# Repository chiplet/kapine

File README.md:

# KAPINE
Kircular Accelerator Prototype Innovative New Experience

# Setup

## KiCAD Library Setup
Run the following command to install the third party KiCAD libraries used in the project

`git submodule update --init --recursive`

This project uses components from [digikey-kicad-library](https://github.com/Digi-Key/digikey-kicad-library) which is configured as a git submodule of this project. Git doesn't clone submodules of a project by default when the project it is cloned so this has to be done manually.

# Hardware

## Pinout

**Application Signal Descriptions**
* m[0..15] -- Electromagnet control signals
* s[0..15] -- Photogate sensor input signals
* Debug 1 -- Debug led 1
* Debug 2 -- Debug led 2
* USART1 -- Command link UART

| Microcontroller Pin | Application Signal | Direction   | Alternate Function |
|---------------------|--------------------|-------------|--------------------|
| PB5                 | m0                 | Digital out | TBD                |
| PD2                 | m1                 | Digital out | TBD                |
| PC11                | m2                 | Digital out | TBD                |
| PA12                | m3                 | Digital out | TBD                |
| PA8                 | m4                 | Digital out | TBD                |
| PC8                 | m5                 | Digital out | TBD                |
| PC6                 | m6                 | Digital out | TBD                |
| PB14                | m7                 | Digital out | TBD                |
| PB11                | m8                 | Digital out | TBD                |
| PB2                 | m9                 | Digital out | TBD                |
| PC5                 | m10                | Digital out | TBD                |
| ~~PA3~~ PA4         | m11                | Digital out | TBD                |
| PC3                 | m12                | Digital out | TBD                |
| PC1                 | m13                | Digital out | TBD                |
| PB9                 | m14                | Digital out | TBD                |
| PB7                 | m15                | Digital out | TBD                |
| PB4                 | s0                 | Digital in  | TBD                |
| ~~PC12~~ PA3        | s1                 | Digital in  | TBD                |
| PC10                | s2                 | Digital in  | TBD                |
| PA11                | s3                 | Digital in  | TBD                |
| PC9                 | s4                 | Digital in  | TBD                |
| PC7                 | s5                 | Digital in  | TBD                |
| PB15                | s6                 | Digital in  | TBD                |
| PB13                | s7                 | Digital in  | TBD                |
| PB10                | s8                 | Digital in  | TBD                |
| PB1                 | s9                 | Digital in  | TBD                |
| ~~PC4~~ PC14        | s10                | Digital in  | TBD                |
| PA2                 | s11                | Digital in  | TBD                |
| ~~PC2~~ PA5         | s12                | Digital in  | TBD                |
| PC0                 | s13                | Digital in  | TBD                |
| PB8                 | s14                | Digital in  | TBD                |
| PB6                 | s15                | Digital in  | TBD                |
| PA0                 | Debug 1            | Digital out | TBD                |
| PA1                 | Debug 2            | Digital out | TBD                |
| PA9                 | USART1_TX          | Digital out | AF7                |
| PA10                | USART1_RX          | Digital in  | AF7                |
| PC13                | RGB LEDs           | Digital out | TBD                |

### Change Log
* 2021-08-07: STM32F3 maps GPIO to EXTI interrupts based on pin number. The following changes needed to be made to support interrupts on all sensor input pins:
  * m11 (PA3 -> PA4)
  * s2 (PC10 -> PA3)
  * s12 (PC2 -> PA5)
  * s10 (PC4 -> PC14)

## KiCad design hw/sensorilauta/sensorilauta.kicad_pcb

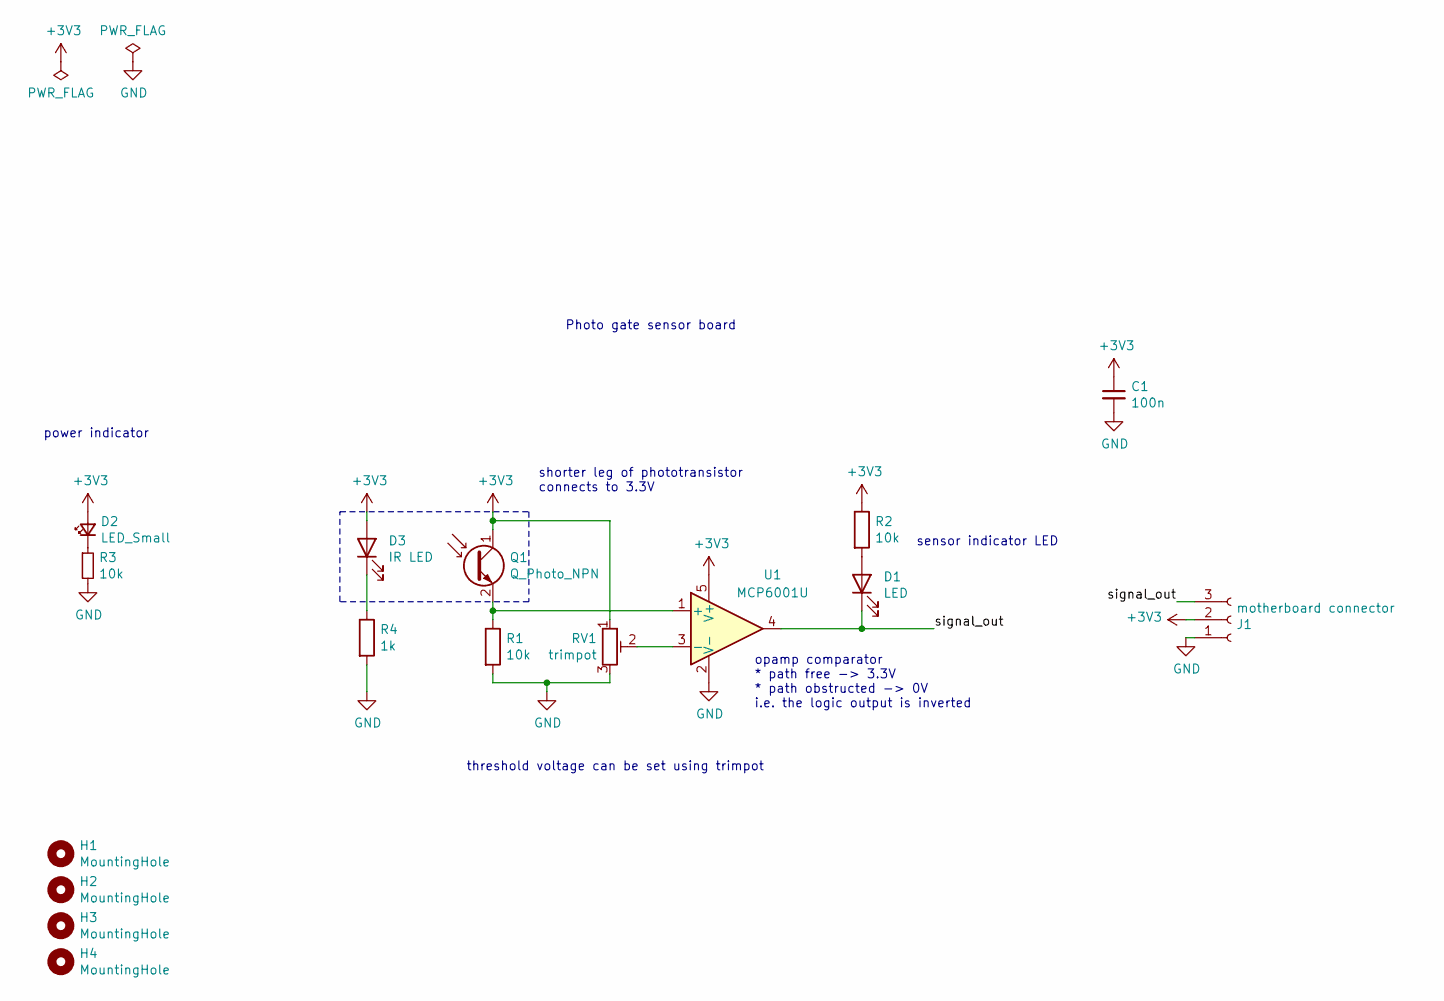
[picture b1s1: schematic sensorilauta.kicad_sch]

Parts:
C1: 100n; C_0805_2012Metric_Pad1.15x1.40mm_HandSolder
D1: LED; LED_D5.0mm
D2: LED_Small; LED_0805_2012Metric_Castellated
D3: IR LED; PinHeader_2x01_P2.54mm_Vertical
H1, H2, H3, H4: MountingHole; MountingHole_4.3mm_M4
J1: motherboard connector; PinHeader_1x03_P2.54mm_Horizontal
Q1: Q_Photo_NPN; PinHeader_2x01_P2.54mm_Vertical
R1, R2, R3: 10k; R_0805_2012Metric_Pad1.15x1.40mm_HandSolder
R4: 1k; R_0805_2012Metric_Pad1.15x1.40mm_HandSolder
RV1: trimpot; Potentiometer_Vishay_TS53YJ_Vertical
U1: MCP6001U; SOT-23-5_HandSoldering

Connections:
+3V3: C1.1, D2.2 (A), D3.2 (A), J1.2, Q1.1 (C), R2.1, RV1.1, U1.5 (V+)
/signal_out: D1.1 (K), J1.3, U1.4
GND: C1.2, J1.1, R1.2, R3.2, R4.2, RV1.3, U1.2 (V-)
unnamed: D1.2 (A), R2.2
unnamed: D2.1 (K), R3.1
unnamed: D3.1 (K), R4.1
unnamed: Q1.2 (E), R1.1, U1.1 (+)
unnamed: RV1.2, U1.3 (-)

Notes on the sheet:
power indicator
sensor indicator LED
threshold voltage can be set using trimpot
Photo gate sensor board
opamp comparator * path free -> 3.3V * path obstructed -> 0V i.e. the logic output is inverted
shorter leg of phototransistor connects to 3.3V

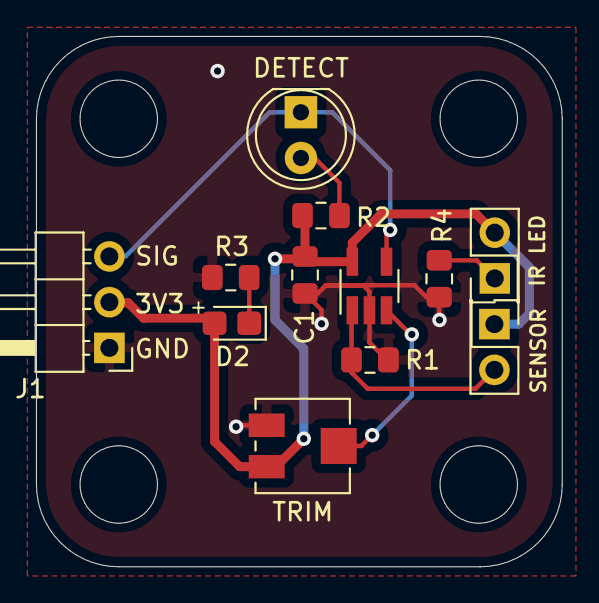
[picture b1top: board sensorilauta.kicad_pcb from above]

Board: 2 copper layers, 29.2 x 29.5 mm, 16 parts (0 on the bottom side), 8 nets.

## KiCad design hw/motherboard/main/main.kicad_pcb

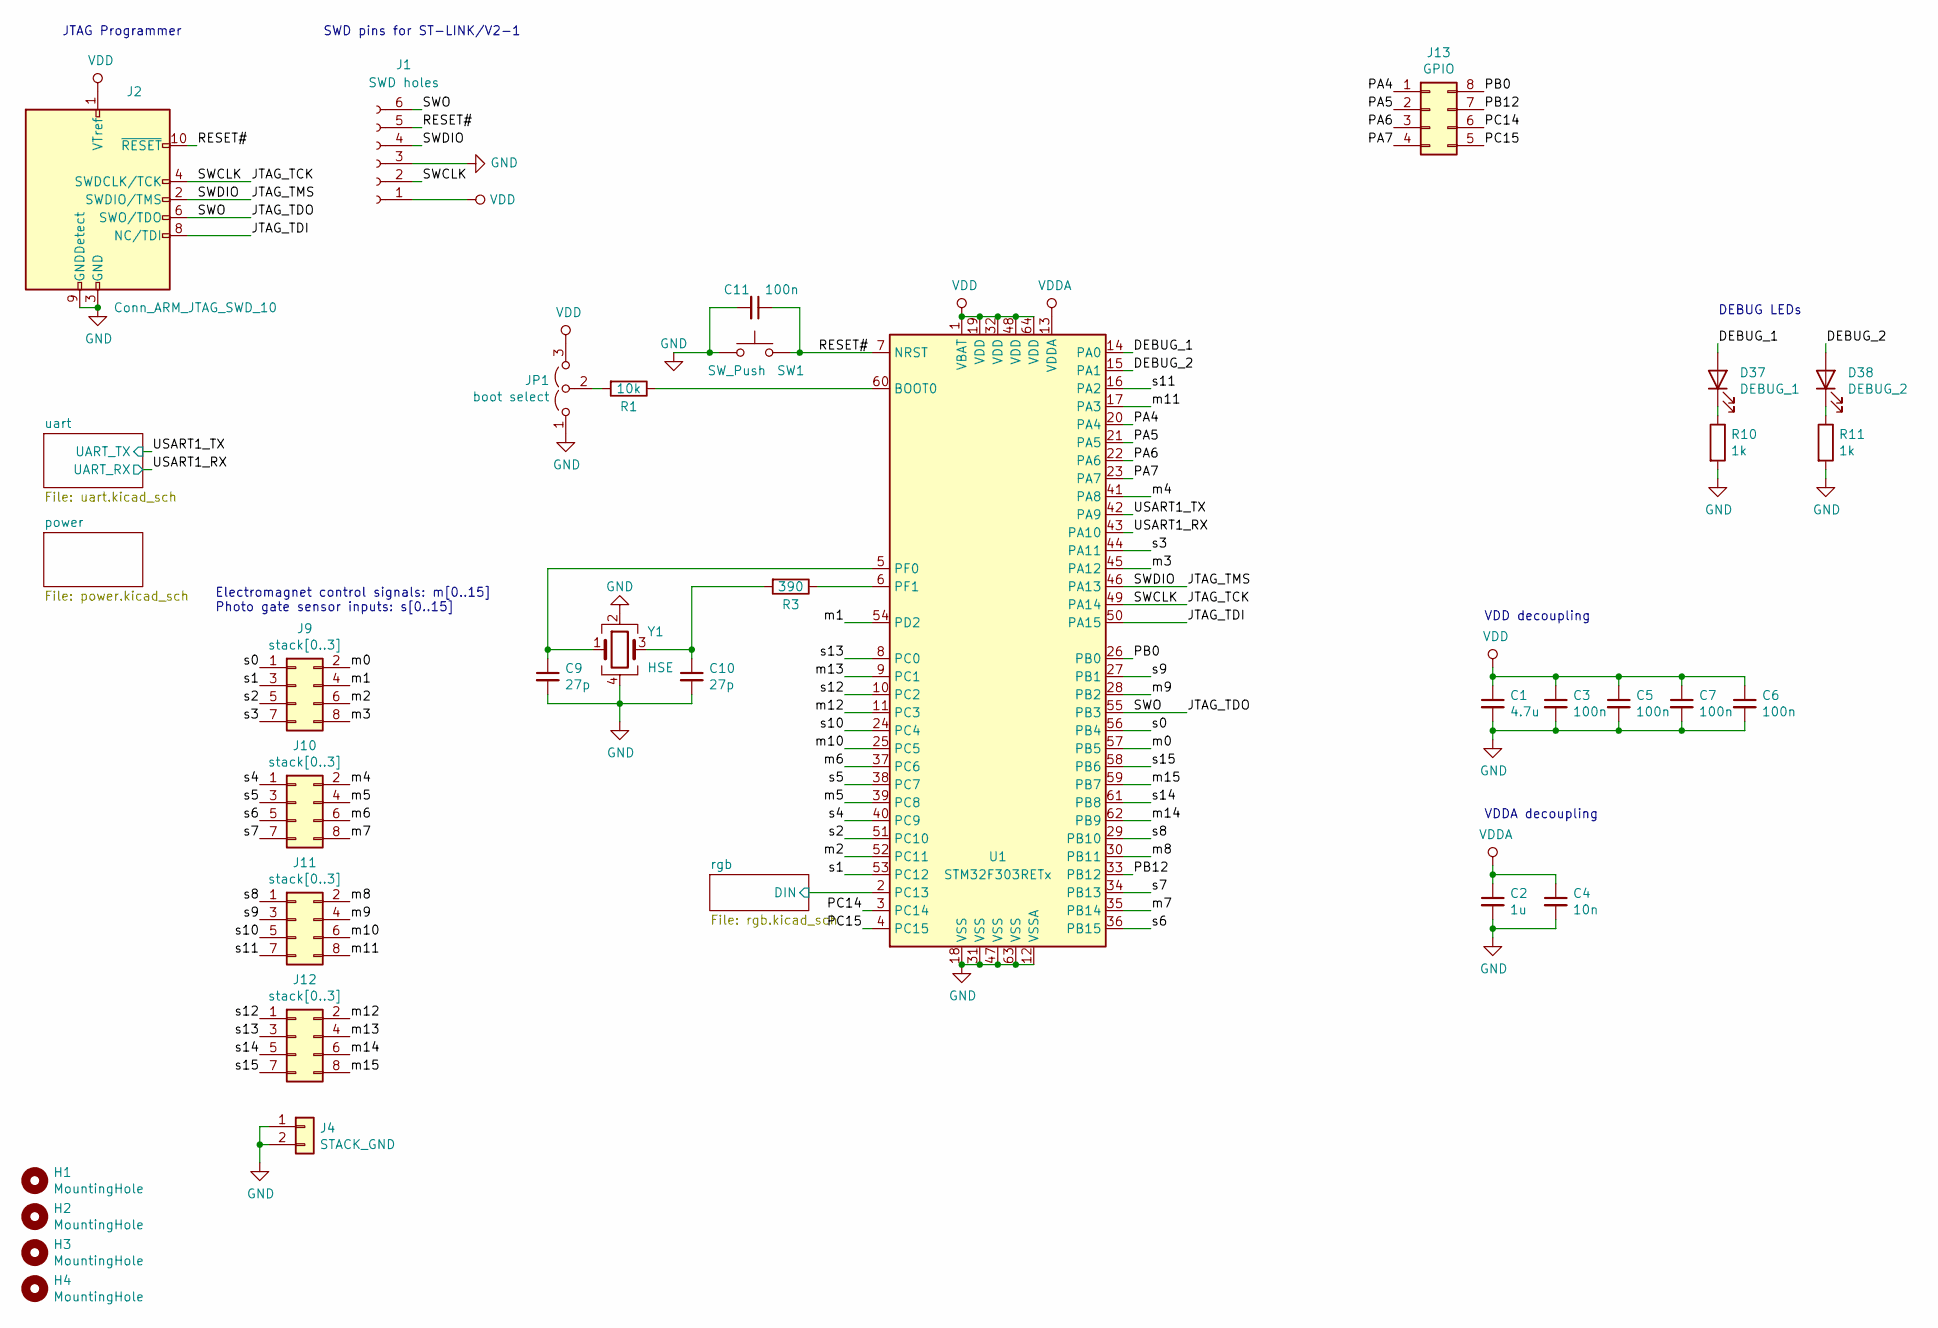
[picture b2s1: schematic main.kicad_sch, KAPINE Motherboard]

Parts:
C1: 4.7u; C_0805_2012Metric
C2: 1u; C_0603_1608Metric
C3, C5, C6, C7, C11: 100n; C_0603_1608Metric
C4: 10n; C_0603_1608Metric
C9, C10: 27p; C_0603_1608Metric
D37: DEBUG_1; LED_0805_2012Metric
D38: DEBUG_2; LED_0805_2012Metric
H1, H2, H3, H4: MountingHole; MountingHole_4.3mm_M4
J1: SWD holes; PinHeader_1x06_P2.54mm_Vertical
J2: Conn_ARM_JTAG_SWD_10; PinHeader_2x5_P1.27mm_Drill.7mm
J4: STACK_GND; PinSocket_1x02_P2.54mm_Vertical
J9, J10, J11, J12: stack[0..3]; PinSocket_2x04_P2.54mm_Vertical
J13: GPIO; PinHeader_2x04_P2.54mm_Vertical
JP1: boot select; PinHeader_1x03_P2.54mm_Vertical
R1: 10k; R_0603_1608Metric
R3: 390; R_0603_1608Metric
R10, R11: 1k; R_0805_2012Metric
SW1: SW_Push; SW_SPST_TL3342
U1: STM32F303RETx; LQFP-64_10x10mm_P0.5mm
Y1: HSE; Crystal_SMD_Abracon_ABM3C-4Pin_5.0x3.2mm

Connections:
/DEBUG_1: D37.2 (A), U1.14 (PA0)
/DEBUG_2: D38.2 (A), U1.15 (PA1)
/JTAG_TCK: J1.2, J2.4 (SWDCLK/TCK), U1.49 (PA14)
/JTAG_TDI: J2.8 (NC/TDI), U1.50 (PA15)
/JTAG_TDO: J1.6, J2.6 (SWO/TDO), U1.55 (PB3)
/JTAG_TMS: J1.4, J2.2 (SWDIO/TMS), U1.46 (PA13)
/PA4: J13.1, U1.20 (PA4)
/PA5: J13.2, U1.21 (PA5)
/PA6: J13.3, U1.22 (PA6)
/PA7: J13.4, U1.23 (PA7)
/PB0: J13.8, U1.26 (PB0)
/PB12: J13.7, U1.33 (PB12)
/PC14: J13.6, U1.3 (PC14)
/PC15: J13.5, U1.4 (PC15)
/RESET#: C11.1, J1.5, J2.10 (~RESET), SW1.2, U1.7 (NRST)
/USART1_RX: U1.43 (PA10); also elsewhere on the board
/USART1_TX: U1.42 (PA9); also elsewhere on the board
/m0: J9.2, U1.57 (PB5)
/m1: J9.4, U1.54 (PD2)
/m2: J9.6, U1.52 (PC11)
/m3: J9.8, U1.45 (PA12)
/m4: J10.2, U1.41 (PA8)
/m5: J10.4, U1.39 (PC8)
/m6: J10.6, U1.37 (PC6)
/m7: J10.8, U1.35 (PB14)
/m8: J11.2, U1.30 (PB11)
/m9: J11.4, U1.28 (PB2)
/m10: J11.6, U1.25 (PC5)
/m11: J11.8, U1.17 (PA3)
/m12: J12.2, U1.11 (PC3)
/m13: J12.4, U1.9 (PC1)
/m14: J12.6, U1.62 (PB9)
/m15: J12.8, U1.59 (PB7)
/rgb/DIN: U1.2 (PC13); also elsewhere on the board
/s0: J9.1, U1.56 (PB4)
/s1: J9.3, U1.53 (PC12)
/s2: J9.5, U1.51 (PC10)
/s3: J9.7, U1.44 (PA11)
/s4: J10.1, U1.40 (PC9)
/s5: J10.3, U1.38 (PC7)
/s6: J10.5, U1.36 (PB15)
/s7: J10.7, U1.34 (PB13)
/s8: J11.1, U1.29 (PB10)
/s9: J11.3, U1.27 (PB1)
/s10: J11.5, U1.24 (PC4)
/s11: J11.7, U1.16 (PA2)
/s12: J12.1, U1.10 (PC2)
/s13: J12.3, U1.8 (PC0)
/s14: J12.5, U1.61 (PB8)
/s15: J12.7, U1.58 (PB6)
GND: C1.2, C2.2, C3.2, C4.2, C5.2, C6.2, C7.2, C9.2, C10.2, C11.2, J1.3, J2.3 (GND), J2.5 (GND), J2.9 (GNDDetect), J4.1, J4.2, JP1.1 (A), R10.2, R11.2, SW1.1, U1.12 (VSSA), U1.18 (VSS), U1.31 (VSS), U1.47 (VSS), U1.63 (VSS), Y1.2, Y1.4; also elsewhere on the board
unnamed: C9.1, U1.5 (PF0), Y1.1
unnamed: C10.1, R3.2, Y1.3
unnamed: D37.1 (K), R10.1
unnamed: D38.1 (K), R11.1
unnamed: JP1.2 (C), R1.2
unnamed: R1.1, U1.60 (BOOT0)
unnamed: R3.1, U1.6 (PF1)
VDD: C1.1, C3.1, C5.1, C6.1, C7.1, J1.1, J2.1 (VTref), JP1.3 (B), U1.1 (VBAT), U1.19 (VDD), U1.32 (VDD), U1.48 (VDD), U1.64 (VDD); also elsewhere on the board
VDDA: C2.1, C4.1, U1.13 (VDDA); also elsewhere on the board

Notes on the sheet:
VDD decoupling
Electromagnet control signals: m[0..15] Photo gate sensor inputs: s[0..15]
SWD pins for ST-LINK/V2-1
JTAG Programmer
DEBUG LEDs
VDDA decoupling

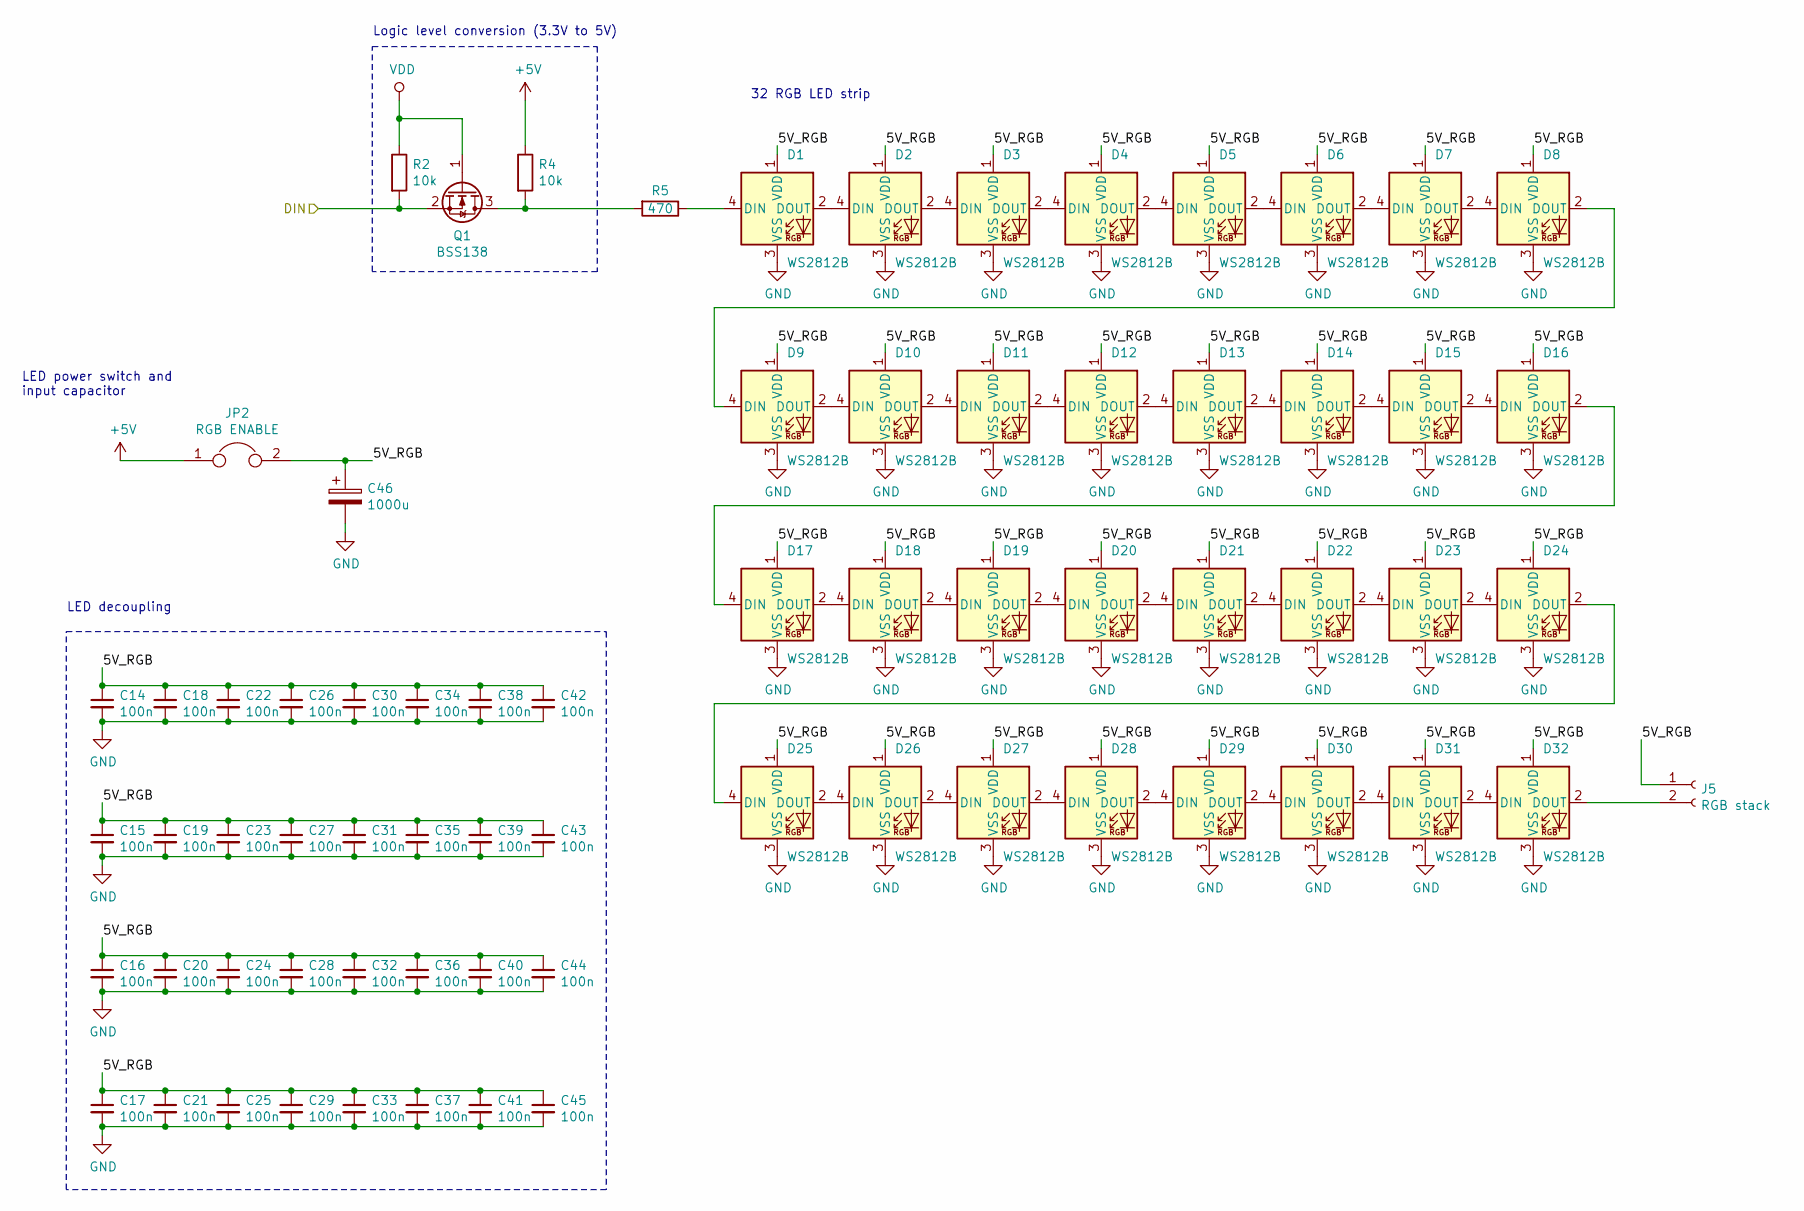
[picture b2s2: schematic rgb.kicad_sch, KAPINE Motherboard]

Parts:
C14, C15, C16, C17, C18, C19, C20, C21, C22, C23, C24, C25, C26, C27, C28, C29, C30, C31, C32, C33, C34, C35, C36, C37, C38, C39, C40, C41, C42, C43, C44, C45: 100n; C_0603_1608Metric
C46: 1000u; CP_Elec_10x10
D1, D2, D3, D4, D5, D6, D7, D8, D9, D10, D11, D12, D13, D14, D15, D16, D17, D18, D19, D20, D21, D22, D23, D24, D25, D26, D27, D28, D29, D30, D31, D32: WS2812B; LED_WS2812B_PLCC4_5.0x5.0mm_P3.2mm
J5: RGB stack; PinSocket_1x02_P2.54mm_Vertical
JP2: RGB ENABLE; PinHeader_1x02_P2.54mm_Vertical
Q1: BSS138; SOT-23
R2, R4: 10k; R_0603_1608Metric
R5: 470; R_0603_1608Metric

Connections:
+5V: JP2.1, R4.1; also elsewhere on the board
/rgb/5V_RGB: C14.1, C15.1, C16.1, C17.1, C18.1, C19.1, C20.1, C21.1, C22.1, C23.1, C24.1, C25.1, C26.1, C27.1, C28.1, C29.1, C30.1, C31.1, C32.1, C33.1, C34.1, C35.1, C36.1, C37.1, C38.1, C39.1, C40.1, C41.1, C42.1, C43.1, C44.1, C45.1, C46.1, D1.1 (VDD), D2.1 (VDD), D3.1 (VDD), D4.1 (VDD), D5.1 (VDD), D6.1 (VDD), D7.1 (VDD), D8.1 (VDD), D9.1 (VDD), D10.1 (VDD), D11.1 (VDD), D12.1 (VDD), D13.1 (VDD), D14.1 (VDD), D15.1 (VDD), D16.1 (VDD), D17.1 (VDD), D18.1 (VDD), D19.1 (VDD), D20.1 (VDD), D21.1 (VDD), D22.1 (VDD), D23.1 (VDD), D24.1 (VDD), D25.1 (VDD), D26.1 (VDD), D27.1 (VDD), D28.1 (VDD), D29.1 (VDD), D30.1 (VDD), D31.1 (VDD), D32.1 (VDD), J5.1, JP2.2
/rgb/DIN: Q1.2 (S), R2.2; also elsewhere on the board
GND: C14.2, C15.2, C16.2, C17.2, C18.2, C19.2, C20.2, C21.2, C22.2, C23.2, C24.2, C25.2, C26.2, C27.2, C28.2, C29.2, C30.2, C31.2, C32.2, C33.2, C34.2, C35.2, C36.2, C37.2, C38.2, C39.2, C40.2, C41.2, C42.2, C43.2, C44.2, C45.2, C46.2, D1.3 (VSS), D2.3 (VSS), D3.3 (VSS), D4.3 (VSS), D5.3 (VSS), D6.3 (VSS), D7.3 (VSS), D8.3 (VSS), D9.3 (VSS), D10.3 (VSS), D11.3 (VSS), D12.3 (VSS), D13.3 (VSS), D14.3 (VSS), D15.3 (VSS), D16.3 (VSS), D17.3 (VSS), D18.3 (VSS), D19.3 (VSS), D20.3 (VSS), D21.3 (VSS), D22.3 (VSS), D23.3 (VSS), D24.3 (VSS), D25.3 (VSS), D26.3 (VSS), D27.3 (VSS), D28.3 (VSS), D29.3 (VSS), D30.3 (VSS), D31.3 (VSS), D32.3 (VSS); also elsewhere on the board
unnamed: D1.2 (DOUT), D2.4 (DIN)
unnamed: D1.4 (DIN), R5.1
unnamed: D2.2 (DOUT), D3.4 (DIN)
unnamed: D3.2 (DOUT), D4.4 (DIN)
unnamed: D4.2 (DOUT), D5.4 (DIN)
unnamed: D5.2 (DOUT), D6.4 (DIN)
unnamed: D6.2 (DOUT), D7.4 (DIN)
unnamed: D7.2 (DOUT), D8.4 (DIN)
unnamed: D8.2 (DOUT), D9.4 (DIN)
unnamed: D10.2 (DOUT), D11.4 (DIN)
unnamed: D9.2 (DOUT), D10.4 (DIN)
unnamed: D11.2 (DOUT), D12.4 (DIN)
unnamed: D12.2 (DOUT), D13.4 (DIN)
unnamed: D13.2 (DOUT), D14.4 (DIN)
unnamed: D14.2 (DOUT), D15.4 (DIN)
unnamed: D15.2 (DOUT), D16.4 (DIN)
unnamed: D16.2 (DOUT), D17.4 (DIN)
unnamed: D17.2 (DOUT), D18.4 (DIN)
unnamed: D18.2 (DOUT), D19.4 (DIN)
unnamed: D19.2 (DOUT), D20.4 (DIN)
unnamed: D20.2 (DOUT), D21.4 (DIN)
unnamed: D21.2 (DOUT), D22.4 (DIN)
unnamed: D22.2 (DOUT), D23.4 (DIN)
unnamed: D23.2 (DOUT), D24.4 (DIN)
unnamed: D24.2 (DOUT), D25.4 (DIN)
unnamed: D25.2 (DOUT), D26.4 (DIN)
unnamed: D26.2 (DOUT), D27.4 (DIN)
unnamed: D27.2 (DOUT), D28.4 (DIN)
unnamed: D28.2 (DOUT), D29.4 (DIN)
unnamed: D29.2 (DOUT), D30.4 (DIN)
unnamed: D30.2 (DOUT), D31.4 (DIN)
unnamed: D31.2 (DOUT), D32.4 (DIN)
unnamed: D32.2 (DOUT), J5.2
unnamed: Q1.3 (D), R4.2, R5.2
VDD: Q1.1 (G), R2.1; also elsewhere on the board

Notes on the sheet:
32 RGB LED strip
LED decoupling
LED power switch and input capacitor
Logic level conversion (3.3V to 5V)

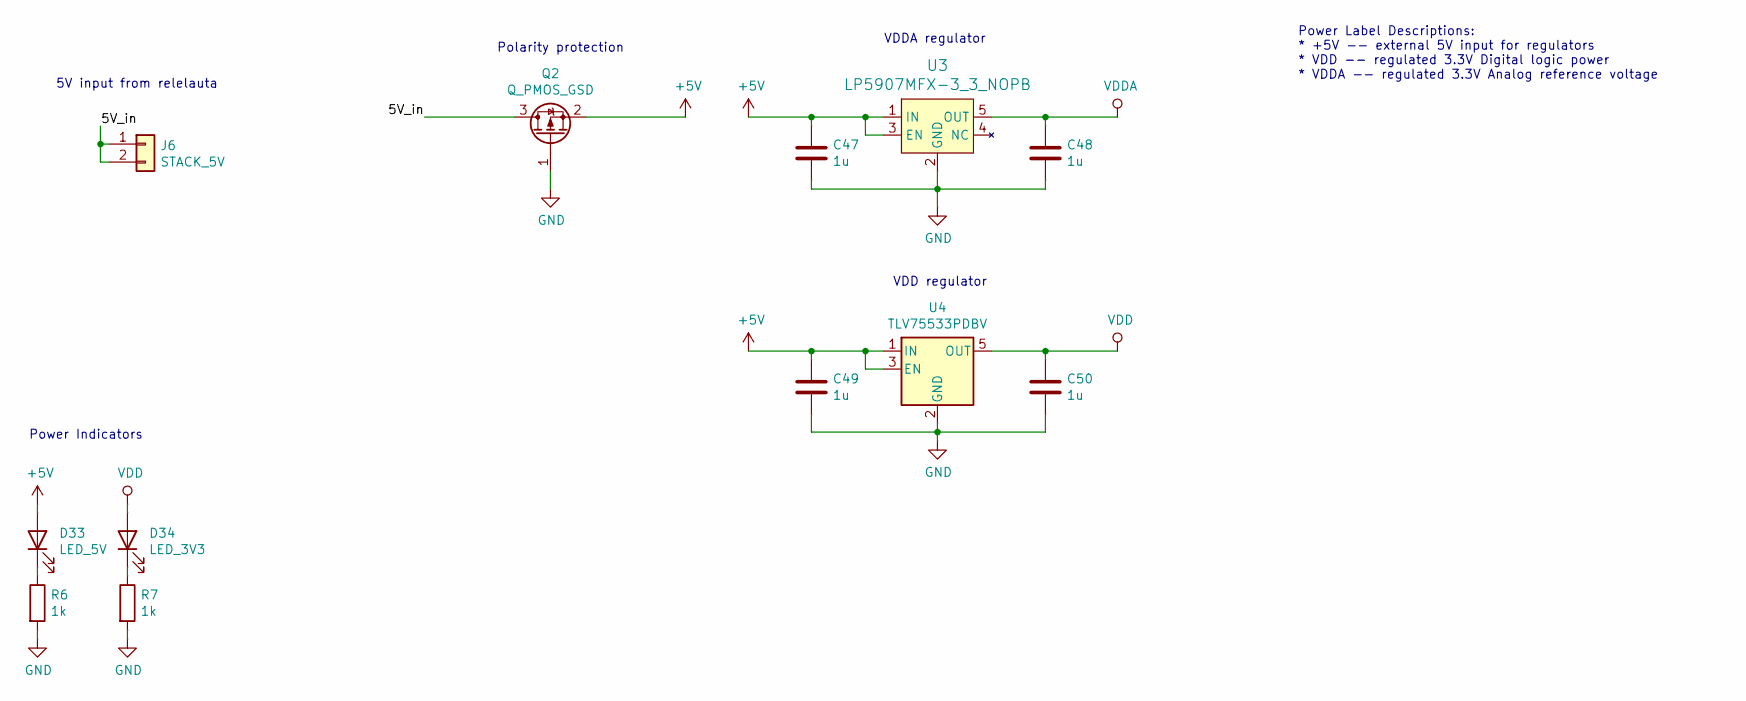
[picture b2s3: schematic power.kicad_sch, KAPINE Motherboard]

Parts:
C47, C48, C49, C50: 1u; C_0603_1608Metric
D33: LED_5V; LED_0805_2012Metric
D34: LED_3V3; LED_0805_2012Metric
J6: STACK_5V; PinSocket_1x02_P2.54mm_Vertical
Q2: Q_PMOS_GSD; SOT-23
R6, R7: 1k; R_0805_2012Metric
U3: LP5907MFX-3_3_NOPB; SOT-753; MPN LP5907MFX-3.3/NOPB; Digi-Key_PN 296-38557-1-ND
U4: TLV75533PDBV; SOT-23-5

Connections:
+5V: C47.1, C49.1, D33.2 (A), Q2.2 (S), U3.1 (IN), U3.3 (EN), U4.1 (IN), U4.3 (EN); also elsewhere on the board
/power/5V_in: J6.1, J6.2, Q2.3 (D)
GND: C47.2, C48.2, C49.2, C50.2, Q2.1 (G), R6.2, R7.2, U3.2 (GND), U4.2 (GND); also elsewhere on the board
unnamed: D33.1 (K), R6.1
unnamed: D34.1 (K), R7.1
VDD: C50.1, D34.2 (A), U4.5 (OUT); also elsewhere on the board
VDDA: C48.1, U3.5 (OUT); also elsewhere on the board

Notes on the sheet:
Power Label Descriptions: * +5V -- external 5V input for regulators * VDD -- regulated 3.3V Digital logic power * VDDA -- regulated 3.3V Analog reference voltage
5V input from relelauta
Polarity protection
VDDA regulator
Power Indicators
VDD regulator

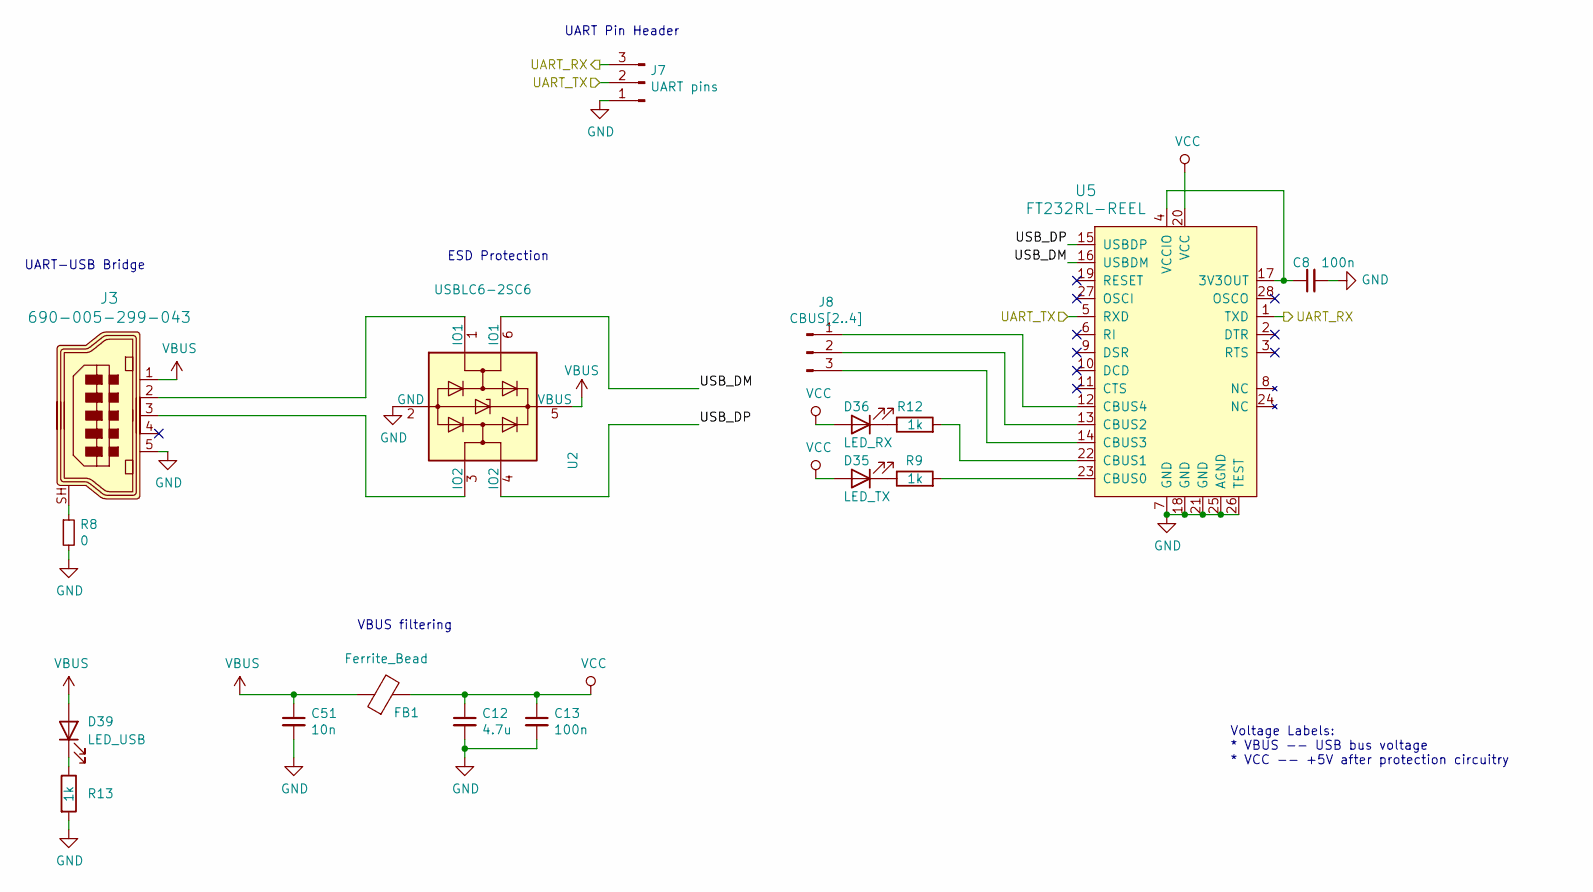
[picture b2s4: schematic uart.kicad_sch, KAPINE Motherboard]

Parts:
C8, C13: 100n; C_0603_1608Metric
C12: 4.7u; C_0805_2012Metric
C51: 10n; C_0603_1608Metric
D35: LED_TX; LED_0805_2012Metric
D36: LED_RX; LED_0805_2012Metric
D39: LED_USB; LED_0805_2012Metric
FB1: Ferrite_Bead; L_0603_1608Metric
J3: 690-005-299-043; USB_Mini_B_Female_690-005-299-043; MPN 690-005-299-043; Digi-Key_PN 151-1206-1-ND
J7: UART pins; PinHeader_1x03_P2.54mm_Vertical
J8: CBUS[2..4]; PinHeader_1x03_P1.27mm_Vertical
R8: 0; R_0603_1608Metric
R9, R12, R13: 1k; R_0805_2012Metric
U2: USBLC6-2SC6; SOT-23-6
U5: FT232RL-REEL; SSOP-28_W5.30mm; MPN FT232RL-REEL; Digi-Key_PN 768-1007-1-ND

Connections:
/USART1_RX: J7.3, U5.1 (TXD); also elsewhere on the board
/USART1_TX: J7.2, U5.5 (RXD); also elsewhere on the board
/uart/USB_DM: U2.6 (IO1), U5.16 (USBDM)
/uart/USB_DP: U2.4 (IO2), U5.15 (USBDP)
GND: C8.2, C12.2, C13.2, C51.2, J3.5, J7.1, R8.2, R13.2, U2.2 (GND), U5.7 (GND), U5.18 (GND), U5.21 (GND), U5.25 (AGND), U5.26 (TEST); also elsewhere on the board
unnamed: C8.1, U5.4 (VCCIO), U5.17 (3V3OUT)
unnamed: D35.1 (K), R9.1
unnamed: D36.1 (K), R12.1
unnamed: D39.1 (K), R13.1
unnamed: J3.2, U2.1 (IO1)
unnamed: J3.3, U2.3 (IO2)
unnamed: J3.SH, R8.1
unnamed: J8.1, U5.12 (CBUS4)
unnamed: J8.2, U5.13 (CBUS2)
unnamed: J8.3, U5.14 (CBUS3)
unnamed: R9.2, U5.23 (CBUS0)
unnamed: R12.2, U5.22 (CBUS1)
VBUS: C51.1, D39.2 (A), FB1.1, J3.1, U2.5 (VBUS)
VCC: C12.1, C13.1, D35.2 (A), D36.2 (A), FB1.2, U5.20 (VCC)

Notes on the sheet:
UART Pin Header
UART-USB Bridge
VBUS filtering
Voltage Labels: * VBUS -- USB bus voltage * VCC -- +5V after protection circuitry
ESD Protection

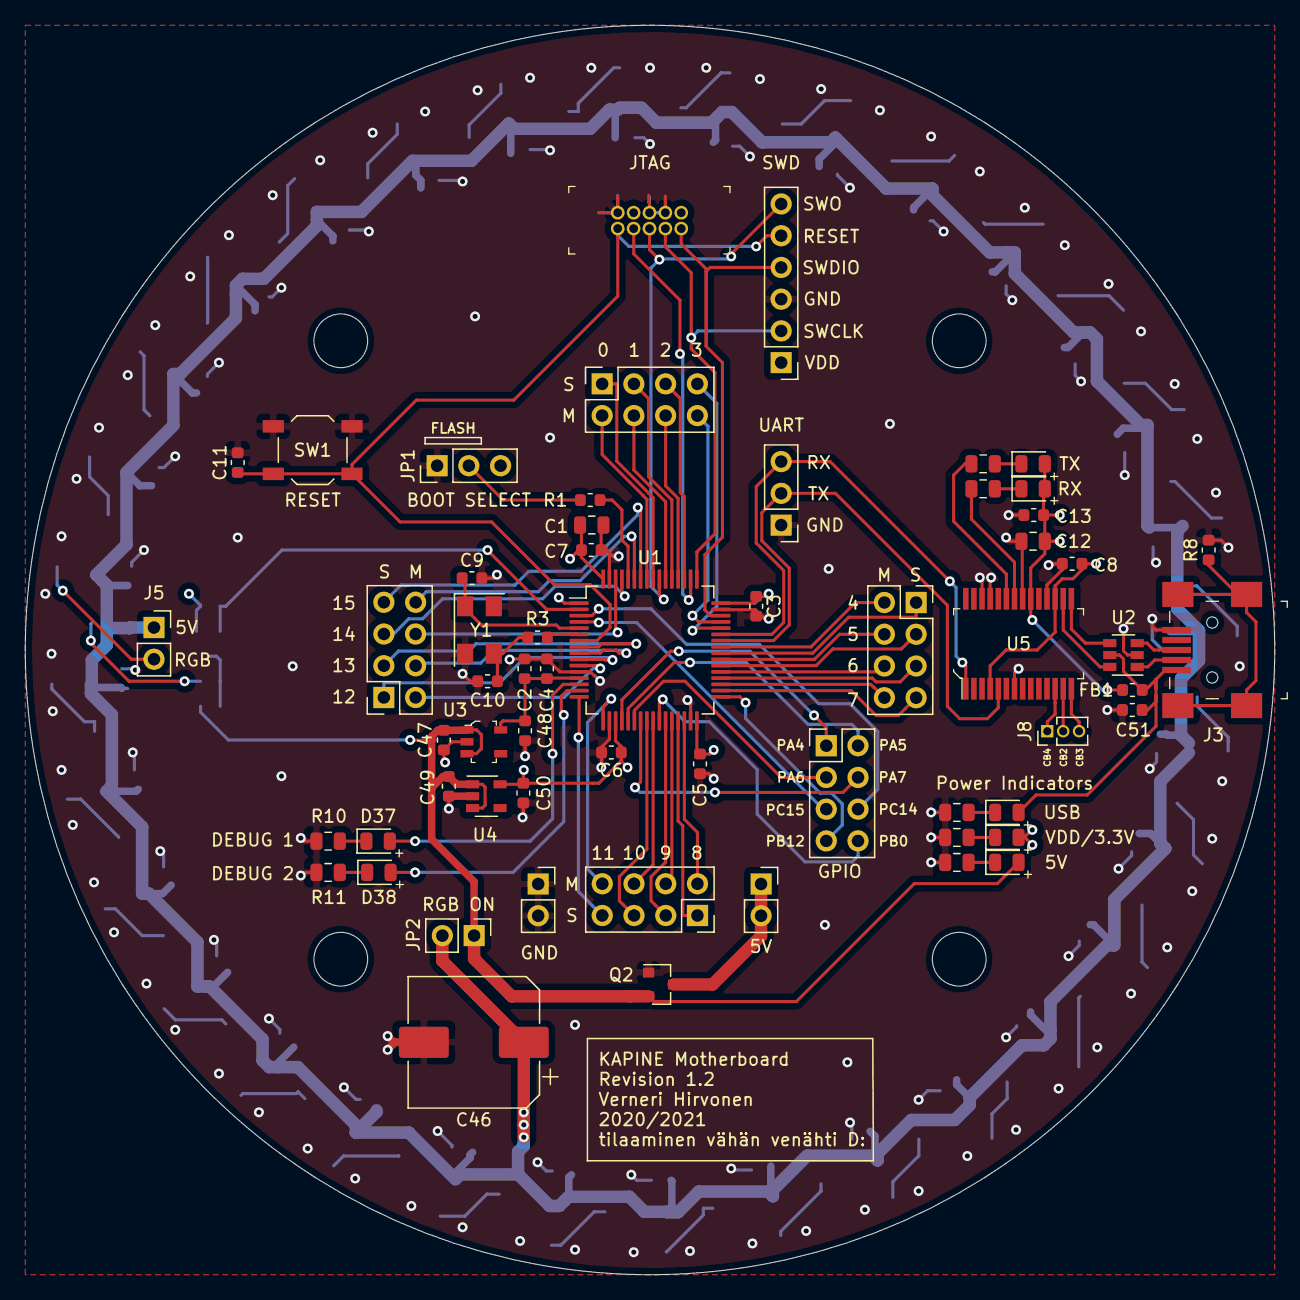
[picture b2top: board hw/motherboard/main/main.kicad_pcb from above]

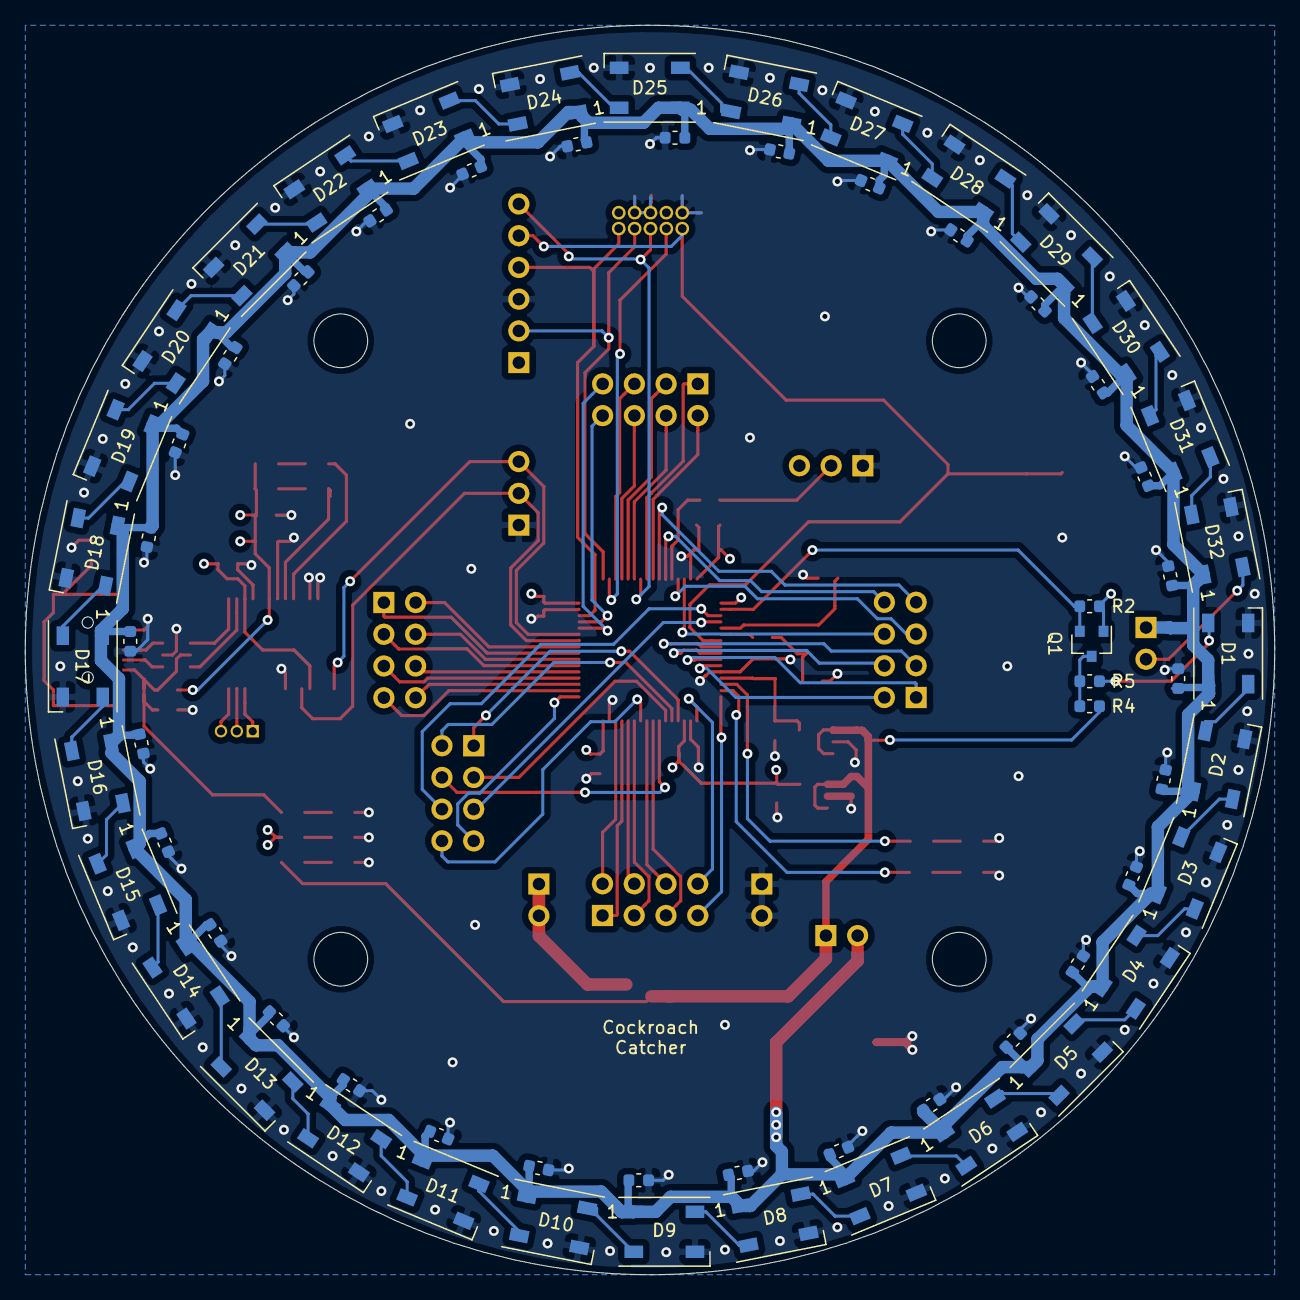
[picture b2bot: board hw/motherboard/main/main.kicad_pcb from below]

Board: 4 copper layers, 100.0 x 100.0 mm, 132 parts (68 on the bottom side), 115 nets.
